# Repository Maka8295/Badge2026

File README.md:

# Tengucon 2026 Badge

The electronic badge for TENGUCON 3.0 (Akihabara, 2026): an ESP32-S3 handheld with a 2.4" SPI display,
a 56-key keyboard, LoRa chat, an IR blaster and receiver, RGB LEDs and a microSD slot, running on a
single-cell LiPo that charges over USB-C.

Hardware designed AI free by Jonathan Black in KiCad, Assembly by Jonathan and Marika Usui.\
Firmware by Djnn, Claude and Jonathan Black.\
Clip-on case by Greg ([Eths33](https://github.com/Eths33)).\
Generously funded by James, Nick and May.

## Hardware

| | |
|-|-|
| MCU | ESP32-S3-WROOM-1-N16R8 (16 MB flash, 8 MB PSRAM) |
| Radio | Ai-Thinker Ra-01SH LoRa module (SX1262, 803-930 MHz) |
| Display | 2.4" SPI TFT on a 50-pin 0.5 mm FPC connector |
| Input | 56-key keyboard matrix on 3× 74LV4051 muxes, 6 game buttons, BOOT and RESET |
| LEDs | 10× SK6803MINI-E addressable RGB, red status LEDs |
| IR | 2× 940 nm LEDs driven by an SS8050, TSOP38238 receiver |
| Storage | microSD (Molex 104031-0811) |
| Power | USB-C, MCP73871 load-sharing Li-Po charger, TPS63020 3.3 V buck-boost, TPS61023 5 V boost |
| PCB | 4 layers, designed in KiCad 10 |

Every BOM part in the schematic has `LCSC`, `Manufacturer` and `Manufacturer Part` fields, and
`production/` holds the JLCPCB fabrication and assembly files.

## Images

### 3D renders

SMD assembly only: the hand-soldered through-hole parts (IR LEDs and the IR receiver socket) are left out.

### Case

A 3D-printable clip-on backing designed by community member Greg ([Eths33](https://github.com/Eths33)).
The STL and STEP files, printing notes and fitting instructions are in [case/](case/).

### PCB editor

### Schematic

## Repository layout

| Path | Contents |
|-|-|
| `badge.kicad_sch`, `badge.kicad_pcb`, `badge.kicad_pro` | KiCad 10 project |
| `3dmodels/` | Project-local 3D models (Ra-01SH, SWPA3015S inductor) |
| `badge.step` | STEP export of the assembled board |
| `production/` | JLCPCB fabrication outputs (Gerbers, BOM, placement) |
| `case/` | 3D-printable clip-on backing by Greg (MIT licence) |
| `firmware/` | Rust firmware, app SDK and tools; see [firmware/README.md](firmware/README.md) |

**Spoiler warning:** `firmware/hunt/` contains the TENGUCON 3.0 scavenger hunt, including all the answers.

## Licence

Copyright © 2026 Jonathan Black.

This project is licensed under [Creative Commons Attribution 4.0 International (CC BY 4.0)](LICENSE).
You may use, modify and redistribute it, including commercially, as long as you give credit, link to
the licence and say what you changed. Please credit it as:

> Tengucon 2026 Badge by Jonathan Black, https://github.com/Maka8295/Badge2026

The case in `case/` was designed by Greg ([Eths33](https://github.com/Eths33)) and is licensed under
the MIT licence; see [case/LICENSE](case/LICENSE).

Other third-party material keeps its own licence and is not covered by CC BY 4.0. This includes the
JetBrains Mono font (SIL OFL, `firmware/tools/fonts/OFL.txt`), the Flipper Zero IR files
(GPL-3.0, `firmware/tools/flipper/SOURCE.txt`), the Phrack issue archive, and sponsor logos and
trademarks.

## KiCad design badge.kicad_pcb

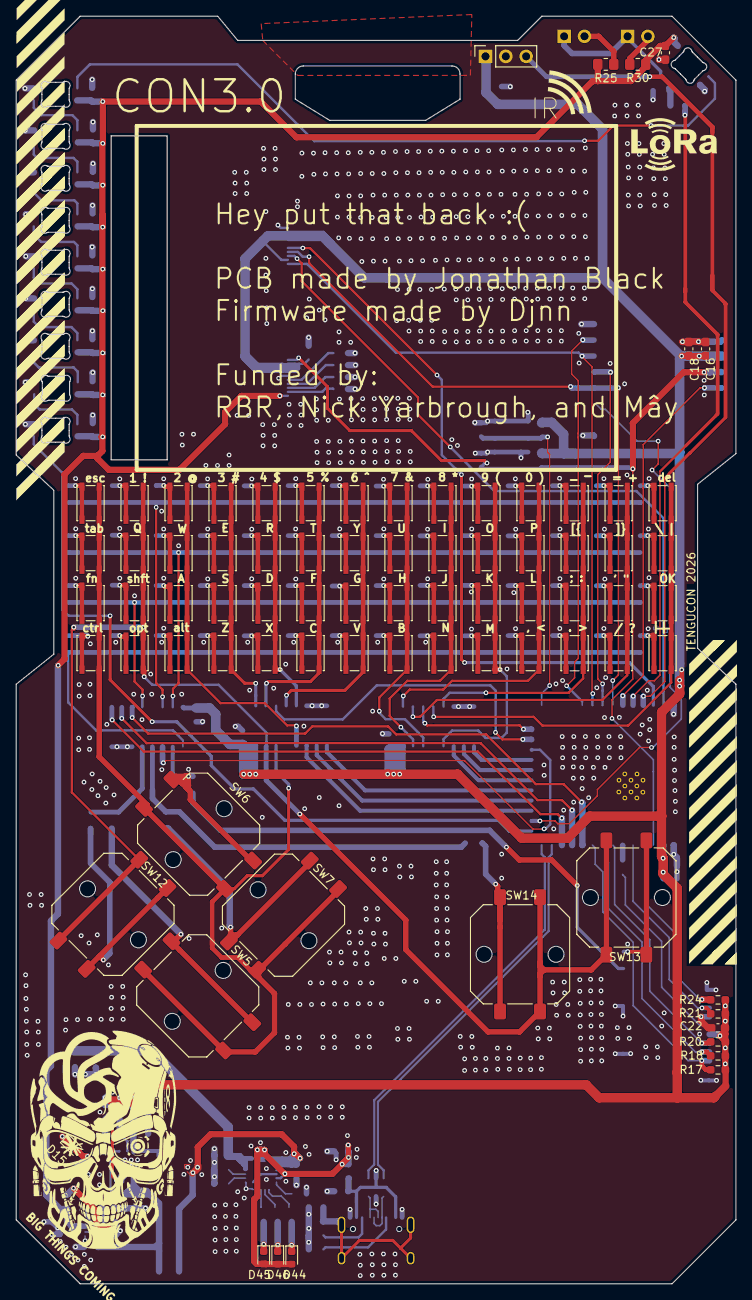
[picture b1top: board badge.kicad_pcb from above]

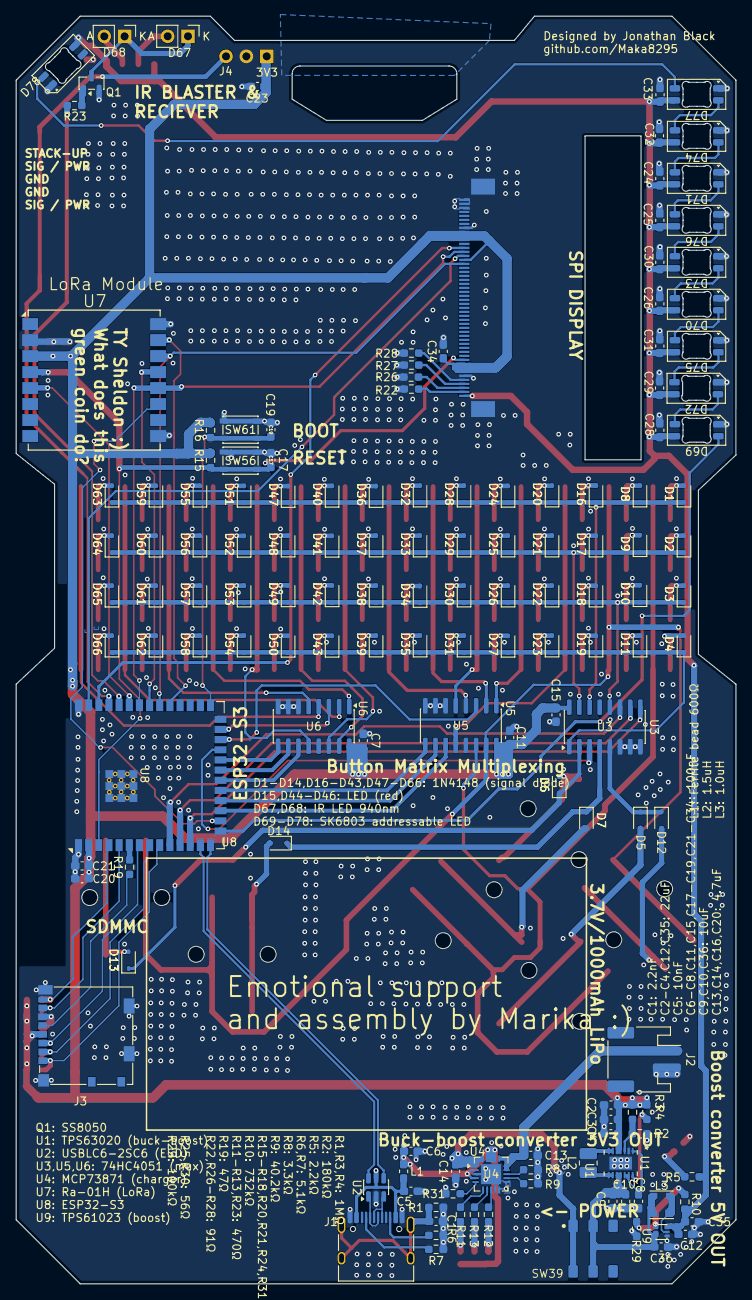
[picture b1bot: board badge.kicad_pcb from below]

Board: 4 copper layers, 90.0 x 158.5 mm, 227 parts (149 on the bottom side), 164 nets.

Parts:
C1: 0603B222K500NT; C_0603_1608Metric_Pad1.08x0.95mm_HandSolder
C2, C3, C4, C12, C35: CL10A226MP8NUNE; C_0603_1608Metric_Pad1.08x0.95mm_HandSolder
C5, C7, C8, C11, C15, C17, C18, C19, C21, C22, C23, C24, C25, C26, C27, C28, C29, C30, C31, C32, C33, C34: CL10B104KA8NNNC; C_0603_1608Metric_Pad1.08x0.95mm_HandSolder
C6, C9, C10, C36: CL10A106MQ8NNNC; C_0603_1608Metric_Pad1.08x0.95mm_HandSolder
C13, C14, C16, C20: CL10A475KP8NNNC; C_0603_1608Metric_Pad1.08x0.95mm_HandSolder
D1, D2, D3, D4, D5, D6, D7, D8, D9, D10, D11, D12, D13, D14, D16, D17, D18, D19, D20, D21, D22, D23, D24, D25, D26, D27, D28, D29, D30, D31, D32, D33, D34, D35, D36, D37, D38, D39, D40, D41, D42, D43, D47, D48, D49, D50, D51, D52, D53, D54, D55, D56, D57, D58, D59, D60, D61, D62, D63, D64, D65, D66: 1N4148WS; D_SOD-323
D15, D44, D45, D46: KT-0603R; LED_0603_1608Metric
D67, D68: 940 5mm LED; PinHeader_1x02_P2.54mm_Vertical
D69, D70, D71, D72, D73, D74, D75, D76, D77, D78: SK6803MINI-E-001; LED_SK6812MINI-E_3.2x2.8mm_P1.5mm_ReverseMount
J1: TYPE-C-31-M-12; USB_C_Receptacle_HRO_TYPE-C-31-M-12
J2: S2B-PH-SM4-TB(LF)(SN); JST_PH_S2B-PH-SM4-TB_1x02-1MP_P2.00mm_Horizontal
J3: 1040310811; microSD_HC_Molex_104031-0811
J4: VISHAY TSOP38238; PinSocket_1x03_P2.54mm_Vertical
J6: F0501-T-50-20T-R; 50pin FPC LCSC
L1: 600R/0.5A; L_0603_1608Metric_Pad1.05x0.95mm_HandSolder
L2: FHD252010S-1R5MT; L_1008_2520Metric_Pad1.43x2.20mm_HandSolder
L3: SWPA3015S1R0NT; L_Coilcraft_LPS3010
Q1: SS8050; SOT-23
R1, R3, R4: 0603WAF1004T5E; R_0603_1608Metric_Pad0.98x0.95mm_HandSolder
R2: CR0603JA0184G; R_0603_1608Metric_Pad0.98x0.95mm_HandSolder
R5: RTT032201FTP; R_0603_1608Metric_Pad0.98x0.95mm_HandSolder
R6, R7: CR0603JA0512G; R_0603_1608Metric_Pad0.98x0.95mm_HandSolder
R8: 3.3k; R_0603_1608Metric_Pad0.98x0.95mm_HandSolder
R9: 40.2k; R_0603_1608Metric_Pad0.98x0.95mm_HandSolder
R10: RTT037323FTP; R_0603_1608Metric_Pad0.98x0.95mm_HandSolder
R11, R12, R13: CR0603FA4700G; R_0603_1608Metric_Pad0.98x0.95mm_HandSolder
R15, R16, R17, R18, R20, R21, R24, R31: WR06X1002FTL; R_0603_1608Metric_Pad0.98x0.95mm_HandSolder
R19: RTT03470JTP; R_0603_1608Metric_Pad0.98x0.95mm_HandSolder
R22, R26, R27, R28: 0603WAF910JT5E; R_0603_1608Metric_Pad0.98x0.95mm_HandSolder
R23: 470R; R_0603_1608Metric_Pad0.98x0.95mm_HandSolder
R25, R30: AC0805FR-7W56RL; R_0805_2012Metric_Pad1.20x1.40mm_HandSolder
R29: RC0603FR-07100KL; R_0603_1608Metric_Pad0.98x0.95mm_HandSolder
SW1, SW2, SW3, SW4, SW8, SW9, SW10, SW11, SW15, SW16, SW17, SW18, SW19, SW20, SW21, SW22, SW23, SW24, SW25, SW26, SW27, SW28, SW29, SW30, SW31, SW32, SW33, SW34, SW35, SW36, SW37, SW38, SW40, SW41, SW42, SW43, SW44, SW45, SW46, SW47, SW48, SW49, SW50, SW51, SW52, SW53, SW54, SW55, SW56, SW57, SW58, SW59, SW60, SW61, SW62, SW63, SW64, SW65: LXW-4X3X2-SMD; SW_SPST_PTS810
SW5, SW6, SW7, SW12, SW13, SW14: TS1103S-12x12x7.3YSMD; SW_Push_1P1T_NO_CK_PTS125Sx73PSMTR
SW39: MST22D18G2 125; SwitchLCSC
U1: TPS63020DSJR; DSJ14_2P85X1P58
U2: USBLC6-2SC6; SOT-23-6
U3, U5, U6: 74HC4051; SOIC-16_3.9x9.9mm_P1.27mm
U4: MCP73871; QFN-20-1EP_4x4mm_P0.5mm_EP2.5x2.5mm
U7: Ra-01SH; Ai-Thinker-Ra-01-LoRa
U8: ESP32-S3-WROOM-2
U9: TPS61023DRLR; SOT-563

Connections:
3V3: C2.2, C3.2, C4.2, C7.1, C11.2, C15.1, C16.1, C18.1, C20.1, C21.1, C22.1, C23.2, C34.1, J3.4 (VDD), J4.1, J6.7, J6.8, J6.9, J6.35, J6.40, J6.41, J6.42, R3.2, R4.2, R15.2, R16.2, R17.2, R18.2, R20.2, R21.2, R24.2, U1.4 (VOUT), U1.5 (VOUT), U3.16 (VCC), U5.16 (VCC), U6.16 (VCC), U7.3 (VDD), U8.2 (3V3)
5V: C12.1, C24.2, C25.2, C26.2, C27.2, C28.2, C29.2, C30.2, C31.2, C32.2, C33.2, C35.1, D69.3 (VDD), D70.3 (VDD), D71.3 (VDD), D72.3 (VDD), D73.3 (VDD), D74.3 (VDD), D75.3 (VDD), D76.3 (VDD), D77.3 (VDD), D78.3 (VDD), J6.1, R5.1, R10.1, R25.1, R30.2, U9.6 (VOUT)
+BATT: C13.1, J2.1, U4.14 (V_{BAT}), U4.15 (V_{BAT}), U4.16 (V_{BAT_SENSE})
BOOT: C19.1, R16.1, SW61.2, U8.27 (IO0)
CMD: J3.3 (CMD), R20.1, U8.7 (IO7)
COL1: SW1.2, SW2.2, SW3.2, SW4.2, SW5.2, SW6.2, SW7.2, U5.14 (A1)
COL2: SW8.2, SW9.2, SW10.2, SW11.2, SW12.2, SW13.2, SW14.2, U5.15 (A2)
COL3: SW15.2, SW16.2, SW17.2, SW18.2, U5.12 (A3)
COL4: SW19.2, SW20.2, SW21.2, SW22.2, U5.1 (A4)
COL5: SW23.2, SW24.2, SW25.2, SW26.2, U5.5 (A5)
COL6: SW27.2, SW28.2, SW29.2, SW30.2, U5.2 (A6)
COL7: SW31.2, SW32.2, SW33.2, SW34.2, U5.4 (A7)
COL8: SW35.2, SW36.2, SW37.2, SW38.2, U6.14 (A1)
COL9: SW40.2, SW41.2, SW42.2, SW43.2, U6.15 (A2)
COL10: SW44.2, SW45.2, SW46.2, SW47.2, U6.12 (A3)
COL11: SW48.2, SW49.2, SW50.2, SW51.2, U6.1 (A4)
COL12: SW52.2, SW53.2, SW54.2, SW55.2, U6.5 (A5)
COL13: SW57.2, SW58.2, SW59.2, SW60.2, U6.2 (A6)
COL14: SW62.2, SW63.2, SW64.2, SW65.2, U6.4 (A7)
COLOUT1: U5.3 (A), U8.24 (IO47)
COLOUT2: U6.3 (A), U8.25 (IO48)
CS1: U7.15 (~NSS), U8.31 (IO38)
CS2: J6.38, U8.38 (IO2)
D+: U2.4 (I/O2), U8.14 (USB_D+/IO20)
D-: U2.6 (I/O1), U8.13 (USB_D-/IO19)
DAT0: J3.7 (DAT0), R21.1, U8.5 (IO5)
DAT1: J3.8 (DAT1), R24.1, U8.4 (IO4)
DAT2: J3.1 (DAT2), R17.1, U8.9 (IO16)
DAT3: J3.2 (DAT3/CD), R18.1, U8.8 (IO15)
EN: C17.1, J6.10, R15.1, SW56.2, U7.4 (~RESET), U8.3 (EN)
GND: C1.1, C2.1, C3.1, C4.1, C5.2, C6.2, C7.2, C8.2, C9.2, C10.2, C11.1, C12.2, C13.2, C14.2, C15.2, C16.2, C17.2, C18.2, C19.2, C20.2, C21.2, C22.2, C23.1, C24.1, C25.1, C26.1, C27.1, C28.1, C29.1, C30.1, C31.1, C32.1, C33.1, C34.2, C35.2, C36.2, D15.1 (K), D69.1 (VSS), D70.1 (VSS), D71.1 (VSS), D72.1 (VSS), D73.1 (VSS), D74.1 (VSS), D75.1 (VSS), D76.1 (VSS), D77.1 (VSS), D78.1 (VSS), J1.A1 (GND), J1.A12 (GND), J1.B1 (GND), J1.B12 (GND), J2.2, J3.6 (VSS), J3.SH (SHIELD), J4.2, J6.6, J6.43, J6.48, J6.49, J6.50, J6.SH, Q1.2 (E), R1.1, R2.2, R6.1, R7.1, R8.2, R9.2, R22.2, R26.2, R27.2, R28.2, R29.2, R31.1, SW56.1, SW61.1, U1.2 (GND), U1.15 (EPAD), U2.2 (GND), U3.6 (~E), U3.7 (VEE), U3.8 (GND), U4.3 (SEL), U4.9 (~TE), U4.10 (V_{SS}), U4.11 (V_{SS}), U4.21 (V_{SS}), U5.6 (~E), U5.7 (VEE), U5.8 (GND), U6.6 (~E), U6.7 (VEE), U6.8 (GND), U7.2 (GND), U7.9 (GND), U7.16 (GND), U8.1 (GND), U8.40 (GND), U8.41 (GND), U9.4 (GND)
IR-IN: J4.3, U8.37 (TXD0/IO43)
IR-OUT: R23.1, U8.36 (RXD0/IO44)
IRO: U7.5 (DIO0), U8.35 (MTMS/IO42)
LED: D69.2 (DIN), U8.15 (IO3)
MISO: U7.13 (MISO), U8.33 (MTDO/IO40)
MOSI: J6.34, U7.14 (MOSI), U8.32 (MTCK/IO39)
unnamed: D1.2 (A), SW1.1
unnamed: D2.2 (A), SW2.1
unnamed: D3.2 (A), SW3.1
unnamed: D4.2 (A), SW4.1
unnamed: D5.2 (A), SW5.1
unnamed: D6.2 (A), SW6.1
unnamed: D7.2 (A), SW7.1
unnamed: D8.2 (A), SW8.1
unnamed: D9.2 (A), SW9.1
unnamed: D10.2 (A), SW10.1
unnamed: D11.2 (A), SW11.1
unnamed: D12.2 (A), SW12.1
unnamed: D13.2 (A), SW13.1
unnamed: D14.2 (A), SW14.1
unnamed: D15.2 (A), R5.2
unnamed: D16.2 (A), SW15.1
unnamed: D17.2 (A), SW16.1
unnamed: D18.2 (A), SW17.1
unnamed: D19.2 (A), SW18.1
unnamed: D20.2 (A), SW19.1
unnamed: D21.2 (A), SW20.1
unnamed: D22.2 (A), SW21.1
unnamed: D23.2 (A), SW22.1
unnamed: D24.2 (A), SW23.1
unnamed: D25.2 (A), SW24.1
unnamed: D26.2 (A), SW25.1
unnamed: D27.2 (A), SW26.1
unnamed: D28.2 (A), SW27.1
unnamed: D29.2 (A), SW28.1
unnamed: D30.2 (A), SW29.1
unnamed: D31.2 (A), SW30.1
unnamed: D32.2 (A), SW31.1
unnamed: D33.2 (A), SW32.1
unnamed: D34.2 (A), SW33.1
unnamed: D35.2 (A), SW34.1
unnamed: D36.2 (A), SW35.1
unnamed: D37.2 (A), SW36.1
unnamed: D38.2 (A), SW37.1
unnamed: D39.2 (A), SW38.1
unnamed: D40.2 (A), SW40.1
unnamed: D41.2 (A), SW41.1
unnamed: D42.2 (A), SW42.1
unnamed: D43.2 (A), SW43.1
unnamed: D44.1 (K), R11.1
unnamed: D45.1 (K), R12.1
unnamed: D46.1 (K), R13.1
unnamed: D47.2 (A), SW44.1
unnamed: D48.2 (A), SW45.1
unnamed: D49.2 (A), SW46.1
unnamed: D50.2 (A), SW47.1
unnamed: D51.2 (A), SW48.1
unnamed: D52.2 (A), SW49.1
unnamed: D53.2 (A), SW50.1
unnamed: D54.2 (A), SW51.1
unnamed: D55.2 (A), SW52.1
unnamed: D56.2 (A), SW53.1
unnamed: D57.2 (A), SW54.1
unnamed: D58.2 (A), SW55.1
unnamed: D59.2 (A), SW57.1
unnamed: D60.2 (A), SW58.1
unnamed: D61.2 (A), SW59.1
unnamed: D62.2 (A), SW60.1
unnamed: D63.2 (A), SW62.1
unnamed: D64.2 (A), SW63.1
unnamed: D65.2 (A), SW64.1
unnamed: D66.2 (A), SW65.1
unnamed: D67.2 (A), R25.2
unnamed: D67.1 (K), D68.1 (K), Q1.3 (C)
unnamed: D68.2 (A), R30.1
unnamed: D69.4 (DOUT), D72.2 (DIN)
unnamed: D70.2 (DIN), D75.4 (DOUT)
unnamed: D70.4 (DOUT), D73.2 (DIN)
unnamed: D71.2 (DIN), D76.4 (DOUT)
unnamed: D71.4 (DOUT), D74.2 (DIN)
unnamed: D72.4 (DOUT), D75.2 (DIN)
unnamed: D73.4 (DOUT), D76.2 (DIN)
unnamed: D74.4 (DOUT), D77.2 (DIN)
unnamed: D77.4 (DOUT), D78.2 (DIN)
unnamed: J1.A5 (CC1), R7.2
unnamed: J1.B5 (CC2), R6.2
unnamed: J1.A6 (D+), J1.B6 (D+), U2.3 (I/O2)
unnamed: J1.A7 (D-), J1.B7 (D-), U2.1 (I/O1)
unnamed: C1.2, J1.SH (SHIELD), R1.2
unnamed: J3.5 (CLK), R19.1
unnamed: J6.2, R22.1
unnamed: J6.3, R26.1
unnamed: J6.4, R27.1
unnamed: J6.5, R28.1
unnamed: L2.1, U1.8 (L1), U1.9 (L1)
unnamed: L2.2, U1.6 (L2), U1.7 (L2)
unnamed: Q1.1 (B), R23.2
unnamed: C8.1, U1.1 (VINA), U1.12 (EN), U1.13 (PS/SYNC)
unnamed: R2.1, R3.1, U1.3 (FB)
unnamed: R4.1, U1.14 (PG)
unnamed: C5.1, J1.A4 (VBUS), J1.A9 (VBUS), J1.B4 (VBUS), J1.B9 (VBUS), L1.2, U2.5 (VBUS)
unnamed: R8.1, U4.13 (PROG1)
unnamed: R9.1, U4.12 (PROG3)
unnamed: R12.2, U4.8 (STAT1/~LBO)
unnamed: R13.2, U4.7 (STAT2)
unnamed: R31.2, U4.5 (THERM)
unnamed: R11.2, U4.6 (~PG)
unnamed: R10.2, R29.1, U9.1 (FB)
unnamed: L3.1, U9.5 (SW)
ROW1: D1.1 (K), D8.1 (K), D16.1 (K), D20.1 (K), D24.1 (K), D28.1 (K), D32.1 (K), D36.1 (K), D40.1 (K), D47.1 (K), D51.1 (K), D55.1 (K), D59.1 (K), D63.1 (K), U3.14 (A1)
ROW2: D2.1 (K), D9.1 (K), D17.1 (K), D21.1 (K), D25.1 (K), D29.1 (K), D33.1 (K), D37.1 (K), D41.1 (K), D48.1 (K), D52.1 (K), D56.1 (K), D60.1 (K), D64.1 (K), U3.15 (A2)
ROW3: D3.1 (K), D10.1 (K), D18.1 (K), D22.1 (K), D26.1 (K), D30.1 (K), D34.1 (K), D38.1 (K), D42.1 (K), D49.1 (K), D53.1 (K), D57.1 (K), D61.1 (K), D65.1 (K), U3.12 (A3)
ROW4: D4.1 (K), D11.1 (K), D19.1 (K), D23.1 (K), D27.1 (K), D31.1 (K), D35.1 (K), D39.1 (K), D43.1 (K), D50.1 (K), D54.1 (K), D58.1 (K), D62.1 (K), D66.1 (K), U3.1 (A4)
ROW5: D5.1 (K), D12.1 (K), U3.5 (A5)
ROW6: D6.1 (K), D13.1 (K), U3.2 (A6)
ROW7: D7.1 (K), D14.1 (K), U3.4 (A7)
ROWOUT: U3.3 (A), U8.23 (IO21)
S0: U3.11 (S0), U8.10 (IO17)
S1: U3.10 (S1), U8.11 (IO18)
S2: U3.9 (S2), U8.12 (IO8)
S3: U5.11 (S0), U8.17 (IO9)
S4: U5.10 (S1), U8.18 (IO10)
S5: U5.9 (S2), U8.19 (IO11)
S6: U6.11 (S0), U8.20 (IO12)
S7: U6.10 (S1), U8.21 (IO13)
S8: U6.9 (S2), U8.22 (IO14)
SDCLK: R19.2, U8.6 (IO6)
SPICLK: J6.37, U7.12 (SCK), U8.34 (MTDI/IO41)
TX/RX: U7.11 (DIO5), U8.16 (IO46)
VBUS: C6.1, D44.2 (A), D45.2 (A), D46.2 (A), L1.1, U4.2 (VPCC), U4.4 (PROG2), U4.17 (CE), U4.18 (IN), U4.19 (IN)
VCHARGE: C14.1, SW39.1 (A), U4.1 (OUT), U4.20 (OUT)
VSWITCH: C9.1, C10.1, C36.1, L3.2, SW39.2 (B), U1.10 (VIN), U1.11 (VIN), U9.2 (EN), U9.3 (VIN)
WRX: J6.36, U8.39 (IO1)

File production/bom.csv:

Comment,Designator,Footprint,JLCPCB Part #
LXW-4X3X2-SMD,"SW1,SW2,SW3,SW4,SW8,SW9,SW10,SW11,SW15,SW16,SW17,SW18,SW19,SW20,SW21,SW22,SW23,SW24,SW25,SW26,SW27,SW28,SW29,SW30,SW31,SW32,SW33,SW34,SW35,SW36,SW37,SW38,SW40,SW41,SW42,SW43,SW44,SW45,SW46,SW47,SW48,SW49,SW50,SW51,SW52,SW53,SW54,SW55,SW57,SW58,SW59,SW60,SW62,SW63,SW64,SW65,SW56,SW61","SMD,4.2x3.4mm",C2888428
CL10B104KA8NNNC,"C18,C22,C27,C7,C8,C11,C15,C17,C19,C21,C23,C24,C25,C26,C28,C29,C30,C31,C32,C33,C34,C5",0603,C14663
F0501-T-50-20T-R,J6,"SMD,P=0.5mm,卧贴",C481229
Ra-01S,U7,"SMD,17x16mm",C2764087
0603WAF1004T5E,"R1,R3,R4",0603,C22935
0603WAF910JT5E,"R22,R26,R27,R28",0603,C25199
CL10A106MQ8NNNC,"C9,C10,C36,C6",0603,C19702
RTT032201FTP,R5,0603,C4190
SS8050,Q1,SOT-23,C7420370
TS1103S-12x12x7.3YSMD,"SW5,SW6,SW7,SW12,SW13,SW14","SMD-4P,12x12mm",C48677737
TPS61023DRLR,U9,SOT-563,C919459
WR06X1002FTL,"R17,R18,R20,R21,R24,R15,R16,R31",0603,C25804
RC0603FR-07100KL,R29,0603,C14675
TYPE-C-31-M-12,J1,SMD,C165948
1040310811,J3,SMD,C585350
0603B222K500NT,C1,0603,C1604
KT-0603R,"D15,D44,D45,D46",0603,C2286
USBLC6-2SC6,U2,SOT-23-6,C2827654
SK6803MINI-E-001,"D69,D70,D71,D72,D73,D74,D75,D76,D77,D78",SMD,C5242955
RTT03470JTP,R19,0603,C23182
CR0603JA0184G,R2,0603,C22827
SWPA3015S1R0NT,L3,"SMD,3x3mm",C43388
TPS63020DSJR,U1,VSON-14-EP(3x4),C15483
CL10A475KP8NNNC,"C16,C13,C14,C20",0603,C1705
MST22D18G2125,SW39,SMD,C2906280
CR0603FA4700G,"R23,R11,R12,R13",0603,C23179
0603WAF3301T5E,R8,0603,C22978
FHD252010S-1R5MT,L2,1008,C602003
CL10A226MP8NUNE,"C2,C3,C4,C12,C35",0603,C86295
MCP73871,U4,QFN-20-EP(4x4),C511310
CR0603JA0512G,"R6,R7",0603,C23186
ESP32-S3-WROOM-2,U8,"SMD,25.5x18mm",C2913202
"74LV4051D,118","U3,U5,U6",SOIC-16,C547978
S2B-PH-SM4-TB(LF)(SN),J2,"SMD,P=2mm,卧贴",C295747
600R/0.5A,L1,0603,C42102
RTT037323FTP,R10,0603,C23239
AC0805FR-7W56RL,"R25,R30",0805,C6117823
40.2kResistor0603,R9,0603,C22369806
1N4148WS,"D1,D2,D3,D4,D5,D6,D7,D8,D9,D10,D11,D12,D13,D14,D16,D17,D18,D19,D20,D21,D22,D23,D24,D25,D26,D27,D28,D29,D30,D31,D32,D33,D34,D35,D36,D37,D38,D39,D40,D41,D42,D43,D47,D48,D49,D50,D51,D52,D53,D54,D55,D56,D57,D58,D59,D60,D61,D62,D63,D64,D65,D66",SOD-323,C2128
